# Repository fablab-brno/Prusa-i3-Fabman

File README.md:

# Prusa i3 Fabman

This repository is mostly dedicated to custom Fabman hardware for Prusa i3 printers.

Fabman.io is all-in-one makerspace management solution and this HW use this service to send amount of filament, name of the file and time of the print to this service. 

This HW was developed by FabLab Brno. You can learn more about our journey <a href="https://hackaday.io/project/166410-access-system-for-3d-printers" target="_blank">here</a>.

We can provide you with complete kit of this HW or you can make your own. All files for production are in this repo. 

We do not share source code for our firmware, but you can easily set it up with you creadentials for Fabman.io . We supply our HW with simple FW which allows you to set things up.    

For this, we use following JSON file: 

```json
{
  "config": {
    "API_key": "device_API_key_from_fabman.io",
	"API_key_master":"admin_API_key_from_fabman.io",
    "nameOfMachine": "custom_name_of_the_machine", 
	"sendName": true,
	"sendFilament": true,
	"sendTime": false,
	"resetSettings": false, 
	"firstSettings": true
  },
  "WiFi": [
    {
      "SSID": "some_wifi",
      "password": "some_password"
    },{
      "SSID": "some_wifi",
      "password": "some_password"
    }
  ]
}
```

For more detailed information, please look at wiki.

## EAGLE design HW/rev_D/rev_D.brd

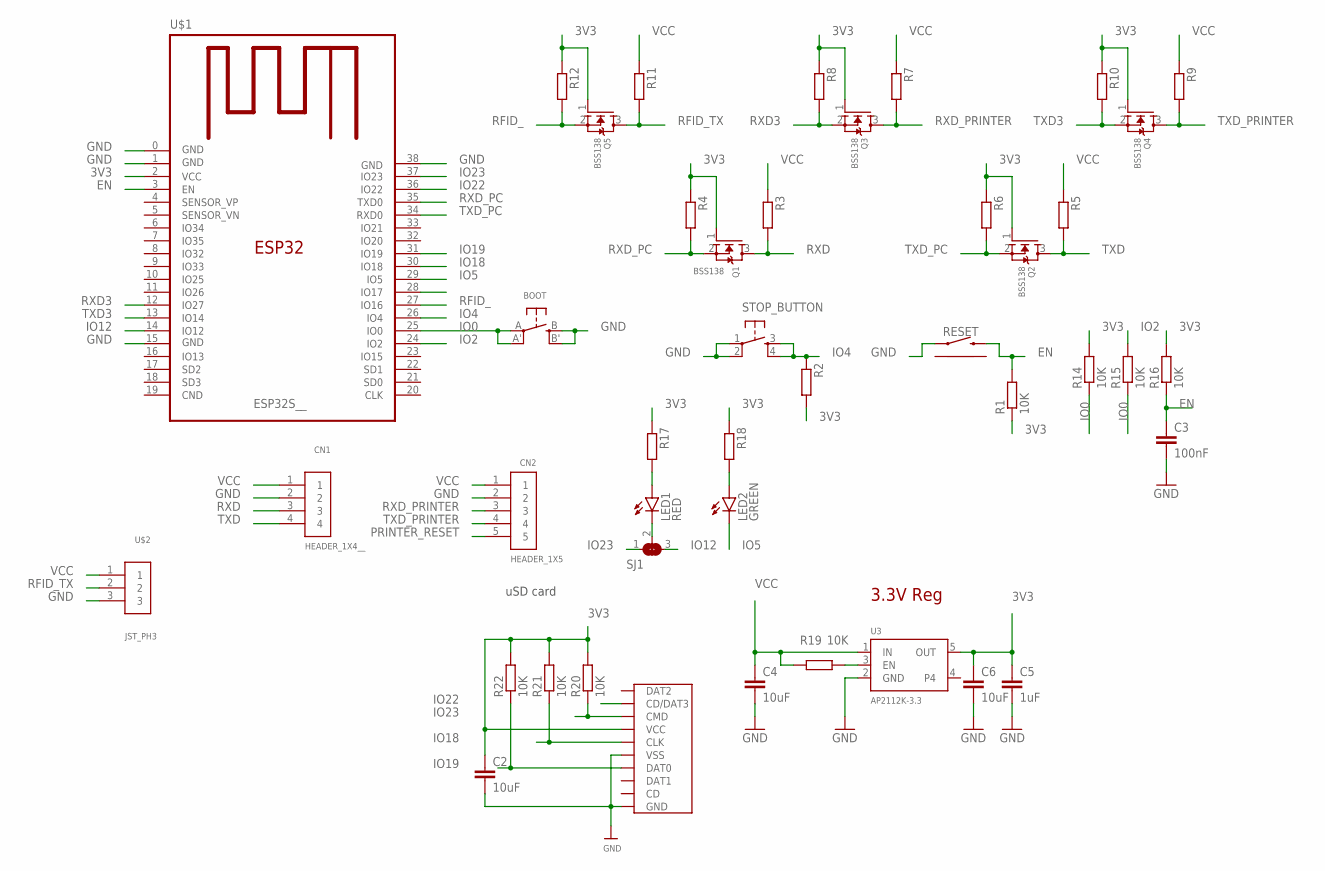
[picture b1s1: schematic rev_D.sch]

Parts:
BOOT: BUTTON_KMR2_4.6X2.8
C2, C4, C6: 10uF; C0805
C3: 100nF; C0805
C5: 1uF; C0805
CN1: HEADER_1X4__; HEADER_1X4_RIGHT_ANGLE
CN2: HEADER_1X5
LED1: RED; CHIP-LED0805
LED2: GREEN; CHIP-LED0805
Q1, Q2, Q3, Q4, Q5: BSS138; SOT95P240X110-3
R1, R2, R3, R4, R5, R6, R7, R8, R9, R10, R11, R12, R14, R15, R16, R19, R20, R21, R22: 10K; R0805
R17, R18: 470R; R0805
RESET: TACTILE_SWITCH_RIGHT_ANGLE_THT_; TACTILE_SWITCH_RIGHT_ANGLE_THT
SD_CARD: MICRO_SD_CARD_; TFP09-2--12B
SJ1: SOLDERJUMPER_2WAY0805; SOLDERJUMPER_2WAY_OPEN_0805
STOP_BUTTON: TACTILE_SWITCH_LONG_THT_; TACTILE_SWICTH_THT
U3: AP2112K-3.3; SOT95P290X120-5
U$1: ESP32S__; ESP32S
U$2: JST_PH3; JST-PH3

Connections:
3V3: C2.1, C5.1, C6.1, Q1.1 (G), Q2.1 (G), Q3.1 (G), Q4.1 (G), Q5.1 (G), R1.1, R2.2, R4.1, R6.1, R8.1, R10.1, R12.1, R14.2, R16.2, R17.1, R18.1, R20.2, R21.2, R22.2, SD_CARD.VCC, U3.5 (OUT), U$1.2 (VCC)
EN: C3.1, R1.2, R16.1, RESET.2, U$1.3 (EN)
GND: BOOT.B (S), BOOT.B' (S1), C2.2, C3.2, C4.2, C5.2, C6.2, CN1.2, CN2.2, RESET.1, SD_CARD.GND, SD_CARD.GND@1 (GND), SD_CARD.GND@2 (GND), SD_CARD.GND@3 (VSS), SD_CARD.VSS (GND), STOP_BUTTON.1, STOP_BUTTON.2, U3.2 (GND), U$1.0 (GND), U$1.1 (GND), U$1.15 (GND), U$1.38 (GND), U$2.3
IO0: BOOT.A, BOOT.A' (P1), R14.1, R15.1, U$1.25 (IO0)
IO2: R15.2, U$1.24 (IO2)
IO4: R2.1, STOP_BUTTON.3, STOP_BUTTON.4, U$1.26 (IO4)
IO5: LED2.C, U$1.29 (IO5)
IO12: SJ1.3, U$1.14 (IO12)
IO18: R21.1, SD_CARD.CLK, U$1.30 (IO18)
IO19: R22.1, SD_CARD.DAT0, U$1.31 (IO19)
IO22: SD_CARD.CD/DAT3, U$1.36 (IO22)
IO23: R20.1, SD_CARD.CMD, SJ1.1, U$1.37 (IO23)
unnamed: LED1.C, SJ1.2
unnamed: LED1.A, R17.2
unnamed: LED2.A, R18.2
unnamed: R19.2, U3.3 (EN)
PRINTER_RESET: CN2.5
RFID_: Q5.2 (S), R12.2, U$1.27 (IO16)
RFID_TX: Q5.3 (D), R11.2, U$2.2
RXD: CN1.3, Q1.3 (D), R3.2
RXD3: Q3.2 (S), R8.2, U$1.12 (IO27)
RXD_PC: Q1.2 (S), R4.2, U$1.35 (TXD0)
RXD_PRINTER: CN2.3, Q3.3 (D), R7.2
TXD: CN1.4, Q2.3 (D), R5.2
TXD3: Q4.2 (S), R10.2, U$1.13 (IO14)
TXD_PC: Q2.2 (S), R6.2, U$1.34 (RXD0)
TXD_PRINTER: CN2.4, Q4.3 (D), R9.2
VCC: C4.1, CN1.1, CN2.1, R3.1, R5.1, R7.1, R9.1, R11.1, R19.1, U3.1 (IN), U$2.1

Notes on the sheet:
3.3V Reg
uSD card

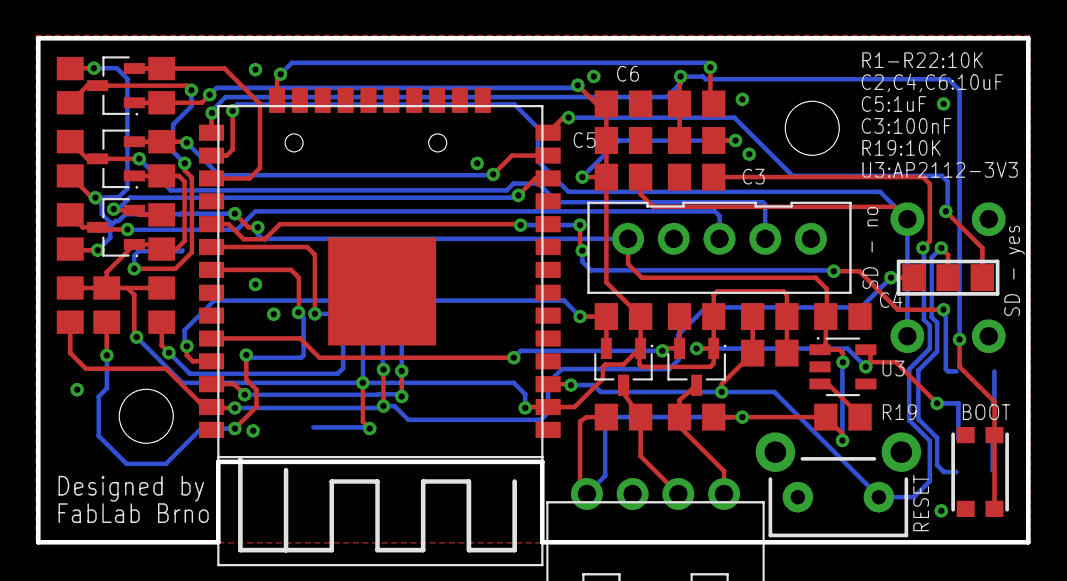
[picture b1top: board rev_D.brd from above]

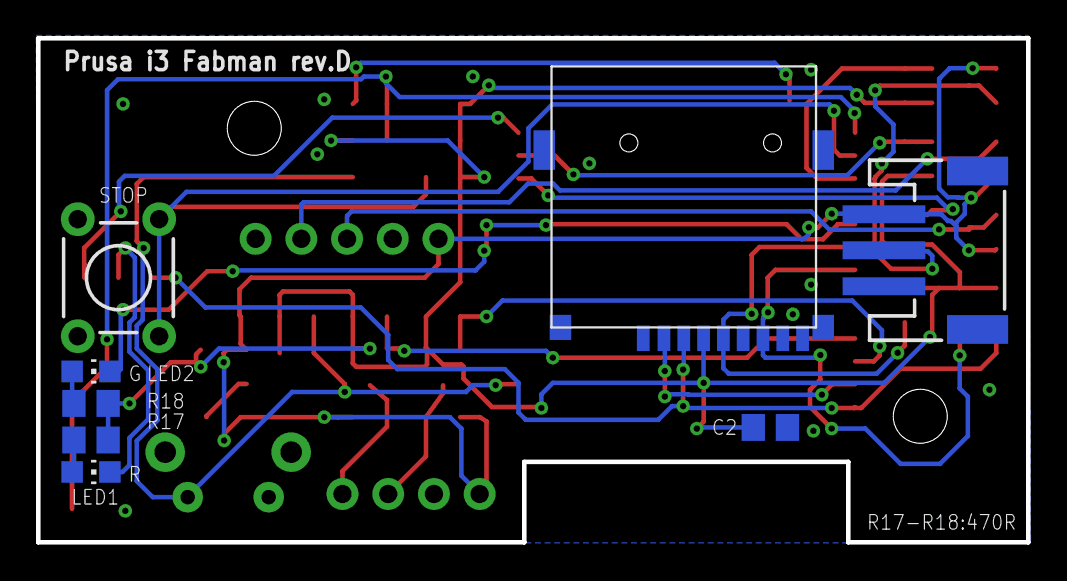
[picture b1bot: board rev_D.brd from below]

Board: 2 copper layers, 55.0 x 28.0 mm, 43 parts (8 on the bottom side), 27 nets.

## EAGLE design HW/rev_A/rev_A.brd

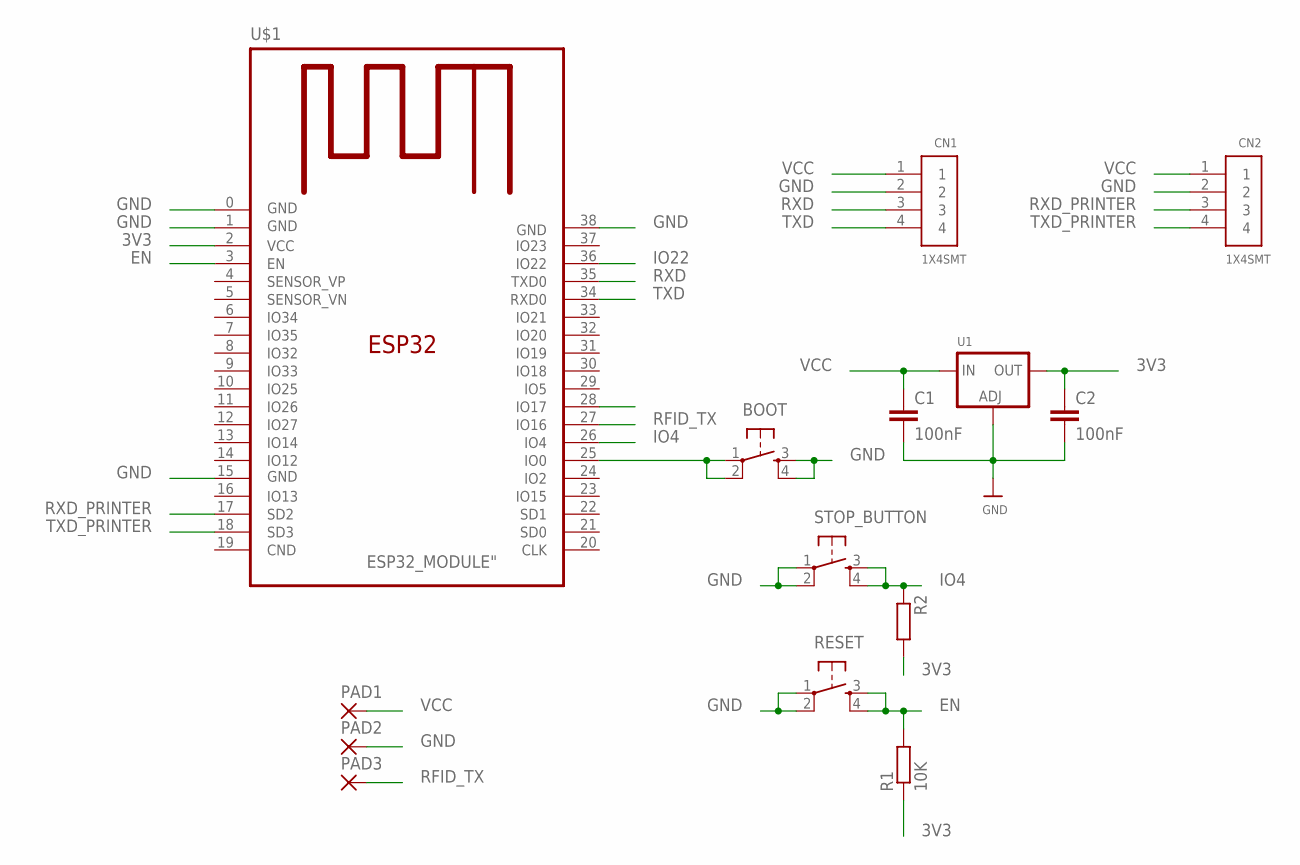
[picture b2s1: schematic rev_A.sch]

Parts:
BOOT: TACTILE_SWITCHE_5X5_MICRO"; TACTILE_SWITCH_5X5_MICRO
C1, C2: 100nF; C0805
CN1, CN2: 1X4SMT; 1X4-SMT
PAD1, PAD2, PAD3: SMD2; SMD1,27-2,54
R1, R2: 10K; R0805
RESET: TACTILE_SWITCHE_5X5_MICRO"; TACTILE_SWITCH_5X5_MICRO
STOP_BUTTON: TACTILE_SWITCH_THT_; TACTILE_SWICTH_THT
U1: LM1117SOT223-REFLOW; SOT223-R
U$1: ESP32_MODULE"; ESP32_MODULE

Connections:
3V3: C2.1, R1.1, R2.2, U1.2 (OUT), U$1.2 (VCC)
EN: R1.2, RESET.3, RESET.4, U$1.3 (EN)
GND: BOOT.3, BOOT.4, C1.2, C2.2, CN1.2, CN2.2, PAD2.1, RESET.1, RESET.2, STOP_BUTTON.1, STOP_BUTTON.2, U1.1 (ADJ), U$1.0 (GND), U$1.1 (GND), U$1.15 (GND), U$1.38 (GND)
IO4: R2.1, STOP_BUTTON.3, STOP_BUTTON.4, U$1.26 (IO4)
IO22: U$1.36 (IO22)
unnamed: BOOT.1, BOOT.2, U$1.25 (IO0)
RFID_TX: PAD3.1, U$1.27 (IO16)
RXD: CN1.3, U$1.35 (TXD0)
RXD_PRINTER: CN2.3, U$1.17 (SD2)
TXD: CN1.4, U$1.34 (RXD0)
TXD_PRINTER: CN2.4, U$1.18 (SD3)
VCC: C1.1, CN1.1, CN2.1, PAD1.1, U1.3 (IN)

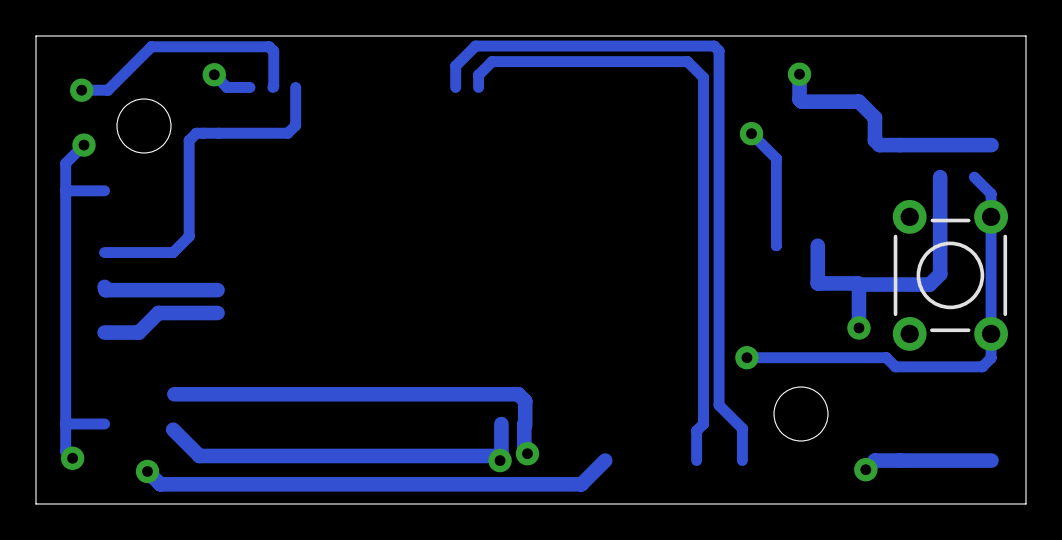
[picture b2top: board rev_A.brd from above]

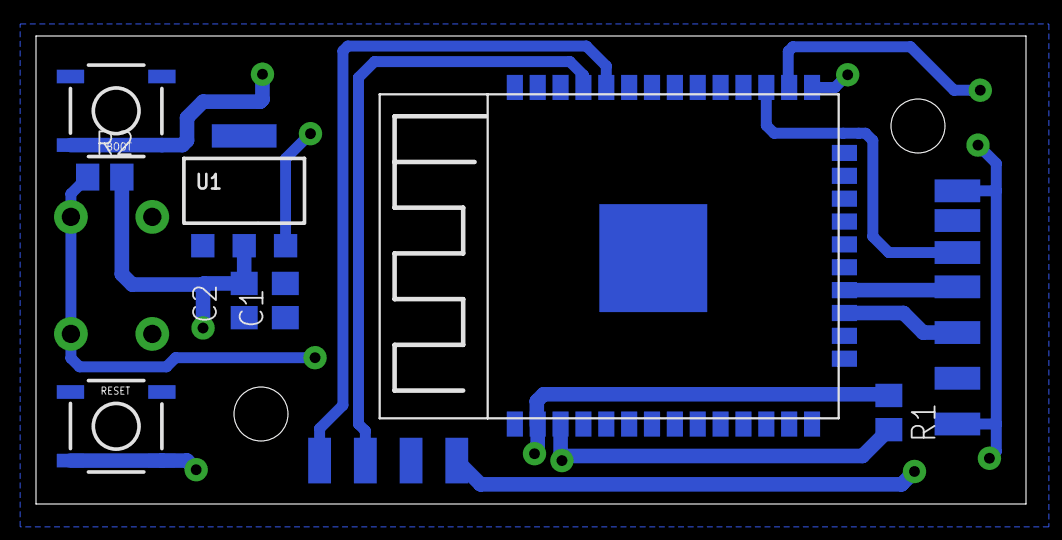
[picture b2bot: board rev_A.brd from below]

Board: 2 copper layers, 55.0 x 26.0 mm, 14 parts (13 on the bottom side), 11 nets.

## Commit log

2019-09-25 Initial commit
    upload of all version
2020-02-24 Files clean up & README update
2020-07-14 Simple FW to test second serial line
2020-07-14 Tools & data to speed up upload of FW

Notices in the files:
parts and their libraries:
microbuilder: This work is placed in the public domain, and may be freely used for commercial and non-commercial work with the following conditions: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
